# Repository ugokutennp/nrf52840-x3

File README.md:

# nrf52840-x3
DIY Multiple Connection Watchman Dongle for SteamVR

## Hardware
It includes data for PCBs made with Kicad7, Gerber data for manufacturing, 3D models of cases, and labels.   
USB2.0 Hub chip with four downstream ports (SL2.1s) running three nrf52840 (MS88SF2) and one USB Type A connector.

BOM can be viewed [here](https://htmlpreview.github.io/?https://github.com/ugokutennp/nrf52840-x3/blob/main/Hardware/PCB/nrf52840_hub.html).Other data are below.

[schematic](images/schematic.pdf),
[layout](images/Layout.png)

## Bootloader

The hex file in the Bootloader file is a build of [Adafruit_nRF52_Bootloader](https://github.com/adafruit/Adafruit_nRF52_Bootloader).
Using J-Link to write the bootloader via SWD, the uf2 firmware created with [Watchman-uf2](https://github.com/ugokutennp/watchman-uf2) can be written via USB.

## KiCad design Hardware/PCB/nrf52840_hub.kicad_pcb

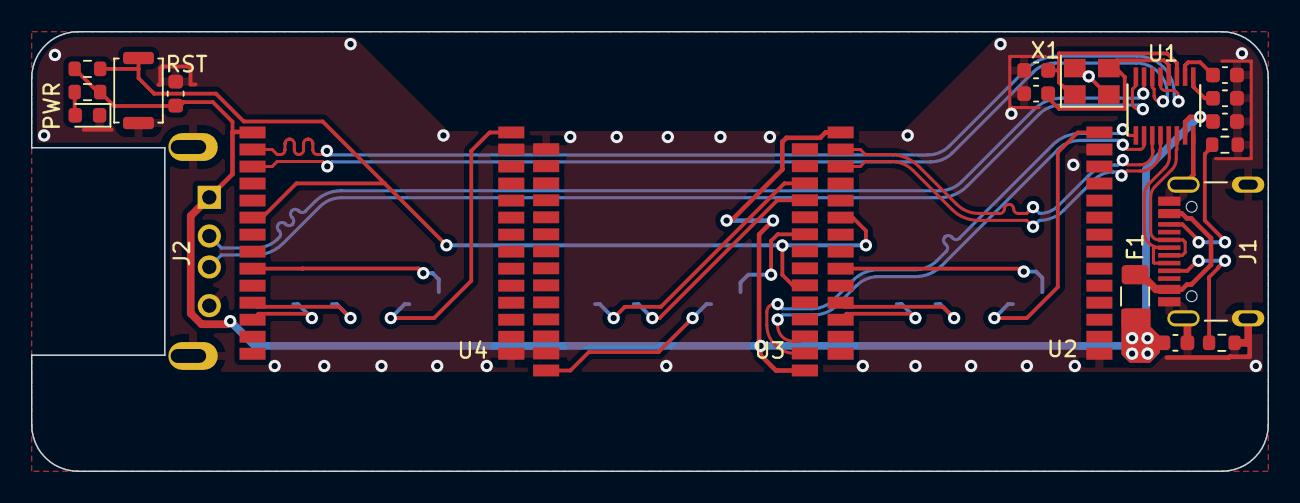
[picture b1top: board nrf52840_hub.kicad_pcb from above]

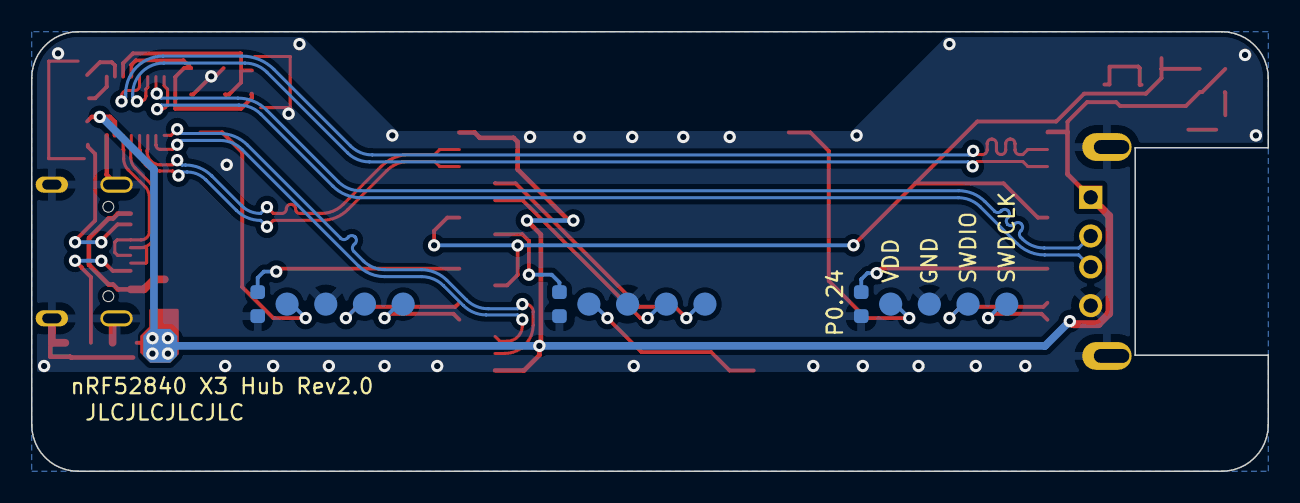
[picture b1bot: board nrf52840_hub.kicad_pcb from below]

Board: 2 copper layers, 79.9 x 28.4 mm, 21 parts (3 on the bottom side), 21 nets.

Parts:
C1, C3, C4: 10u; C_0603_1608Metric
C2: 100ｎ; C_0603_1608Metric
D1: 19-217/BHC-ZL1M2RY/3T; LED_0603_1608Metric
F1: MF-NSMF050-2; Fuse_1206_3216Metric
J1: TYPE-C-31-M-12; HRO_TYPE-C-31-M-12
J2: U-A-24DD-W-16; USB_A_U-A-24DD-W-16
R1, R2: 5k1; R_0603_1608Metric
R4: 470; R_0603_1608Metric
R5: 10k; R_0603_1608Metric
SW1: SKRKAEE020; SW_Push_SPST_NO_Alps_SKRK
U1: SL2.1S; SSOP-16_sl2.1s
U2, U3, U4: MS88SF2; XCVR_MS88SF2
X1: X322512MSB4SI; Crystal_SMD_3225-4Pin_3.2x2.5mm
p0.24, p0.24#2, p0.24#3: C_0603_1608Metric

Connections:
1D_N: U1.3 (DM1), U2.16 (D-)
1D_P: U1.4 (DP1), U2.17 (D+)
2D_N: U1.1 (DM2), U3.16 (D-)
2D_P: U1.2 (DP2), U3.17 (D+)
3D_N: J2.2 (D-), U1.15 (DM3)
3D_P: J2.3 (D+), U1.16 (DP3)
4D_N: U1.13 (DM4), U4.16 (D-)
4D_P: U1.14 (DP4), U4.17 (D+)
+5V: C1.1, C2.1, F1.2, J2.1 (VBUS), R4.1, R5.2, U1.7 (VDD5), U2.15 (VDDH), U3.15 (VDDH), U4.15 (VDDH)
GND: C1.2, C2.2, C3.1, C4.1, D1.1 (K), J1.A1B12 (GND), J1.B1A12 (GND), J1.S1 (SHIELD), J1.S2 (SHIELD), J1.S3 (SHIELD), J1.S4 (SHIELD), J2.4 (GND), J2.5 (Shield), R1.2, R2.2, SW1.2, U1.8 (VSS), U2.1 (GND), U2.13 (GND), U3.1 (GND), U3.13 (GND), U4.1 (GND), U4.13 (GND), X1.2, X1.4, p0.24.1, p0.24#2.1, p0.24#3.1
unnamed: C3.2, U1.9 (VDD33)
unnamed: C4.2, U1.10 (VDD18)
unnamed: D1.2 (A), R4.2
unnamed: F1.1, J1.A4B9 (VBUS), J1.B4A9 (VBUS)
unnamed: J1.A5 (CC1), R1.1
unnamed: J1.B5 (CC2), R2.1
unnamed: U1.11 (XOUT), X1.1
unnamed: U1.12 (XIN), X1.3
RST: R5.1, SW1.1, U2.20 (P0.18/~RESET), U3.20 (P0.18/~RESET), U4.20 (P0.18/~RESET)
UD_N: J1.A7 (DN1), J1.B7 (DN2), U1.5 (UDM)
UD_P: J1.A6 (DP1), J1.B6 (DP2), U1.6 (UDP)

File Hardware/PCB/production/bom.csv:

Designator,Footprint,Quantity,Value,LCSC Part #
"_12, _11, _10, _9, _8, _7, _6, _5, _4, _3, _2, ",,12,,
"C1, C3, C4",0603,3,10u,
C2,0603,1,100ｎ,
D1,0603,1,19-217/BHC-ZL1M2RY/3T,
F1,1206,1,MF-NSMF050-2,
J1,HRO_TYPE-C-31-M-12,1,TYPE-C-31-M-12,
J2,USB_A_U-A-24DD-W-16,1,U-A-24DD-W-16,
"R1, R2",0603,2,5k1,
R4,0603,1,470,
R5,0603,1,10k,
SW1,SW_Push_SPST_NO_Alps_SKRK,1,SKRKAEE020,
U1,SSOP-16_sl2.1s,1,SL2.1S,
"U2, U3, U4",XCVR_MS88SF2,3,MS88SF2,
X1,Crystal_SMD_3225-4Pin_3.2x2.5mm,1,X322512MSB4SI,
